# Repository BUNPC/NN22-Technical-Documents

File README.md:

This repository contains the technical documentation used to create all parts of the NN22 whole-head fNIRS system.

A description of the documents contained in this respository and other instructions related to the ninjaNIRS system can be found at openfnirs.org [here](https://openfnirs.org/hardware/ninjanirs2022/).

Please use the [Hardware Forum](https://openfnirs.org/community/hardware-forum/) at openfnirs.org to discuss anything about the ninjaNIRS system.

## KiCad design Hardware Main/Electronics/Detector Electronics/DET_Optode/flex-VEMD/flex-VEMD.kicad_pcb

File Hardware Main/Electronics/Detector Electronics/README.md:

# Detector Electronics
## Updated 5 August, 2024

All detector related files are located within this folder.

Two versions of the backplane are available, the 6 layer and single layer. The 6 layer folder contains the files for the full height backplane to allow for up to 6 detector interface cards to be connected and the single layer folder contains the files for the system configuration with only one interface card per backboard slot.

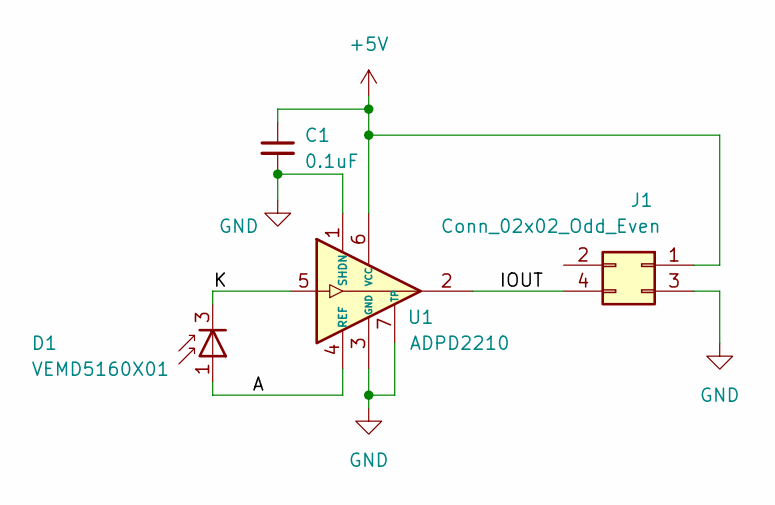
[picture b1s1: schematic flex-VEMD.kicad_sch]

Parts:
C1: 0.1uF; C_0402_1005Metric
D1: VEMD5160X01; VEMD-4-4.1x5.2mm
J1: Conn_02x02_Odd_Even; PinHeader_2x02_P1.27mm_compact
U1: ADPD2210; LFCSP-6-2x2mm

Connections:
+5V: C1.1, J1.1, U1.6 (VCC)
/A: D1.1 (A), U1.4 (REF)
/IOUT: J1.4, U1.2
/K: D1.3 (K), D1.4 (K), U1.5
GND: C1.2, J1.3, U1.1 (SHDN), U1.3 (GND), U1.7 (TP)

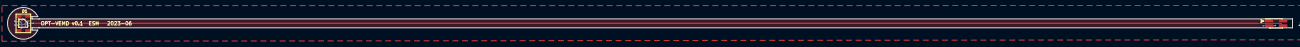
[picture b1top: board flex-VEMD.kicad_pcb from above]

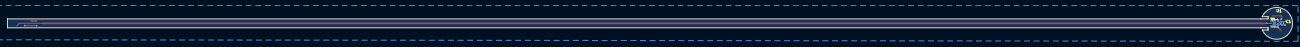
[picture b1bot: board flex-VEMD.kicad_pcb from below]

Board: 2 copper layers, 360.0 x 8.9 mm, 4 parts (2 on the bottom side), 5 nets.

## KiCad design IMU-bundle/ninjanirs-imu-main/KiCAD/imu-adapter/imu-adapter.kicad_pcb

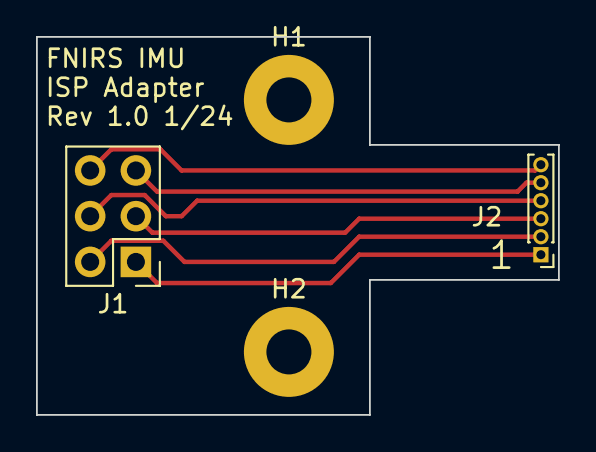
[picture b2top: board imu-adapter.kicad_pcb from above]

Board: 2 copper layers, 29.0 x 21.0 mm, 4 parts (0 on the bottom side), 6 nets.

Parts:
H1, H2: MountingHole; MountingHole_2.5mm_Pad
J1: 2x3_0.1in; PinHeader_2x03_P2.54mm_Vertical
J2: 1mm_SIP; PinHeader_1x06_P1.00mm_Vertical

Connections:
unnamed: J1.6 (GND), J2.6 (GND)
unnamed: J1.1 (MISO), J2.1 (MISO)
unnamed: J1.4 (MOSI), J2.4 (MOSI)
unnamed: J1.3 (SCK), J2.3 (SCK)
unnamed: J1.2 (VCC), J2.2 (VCC)
unnamed: J1.5 (~RST), J2.5 (~RST)

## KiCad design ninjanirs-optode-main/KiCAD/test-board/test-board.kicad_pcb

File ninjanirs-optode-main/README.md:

# ninjaNIRS optode study

  - [Flex board with Vishay photodiode](#flex-board-with-vishay-photodiode)
  - [Flex board with IQ80x photosensor](#flex-board-with-iq80x-photosensor)
  - [Readout box](#readout-box)
    - [Other devices considered](#other-devices-considered)

This repo contains work towards an implementation of an "optode" sensor unit
using off-the-shelf components.

The first design is essentially a mechanical test of the use of inexpensive
flex circuits to implement a complete optode, including connector pigtail.

## Flex board with Vishay photodiode

See `KiCAD/flex-VEMD`.

This board has a VEMD5160X01 photodiode and Analog devices ADPD2210 current amplifier.
Tests showed excessive sensitivity to 60Hz pickup, even with the flexi shielded
with copper tape.  This design has been abandoned for now (late 2023).

JLC double-layer flex has a 25um polyimide dielectric with 0.5oz copper on both sides.
There is 25um adhesive and 25um polyimide cover on each side.  Trace width is 0.5mm
with adjacent GND separated by 0.15mm.  Length 340mm.

PI dielectric constant is 3-4.

```
Parallel plate C = E(A/d) = (k * E0 * A) / d

  k = relative permittivity of dielectric (say, 3.5 for polyimide)
  E0 = permittivity of space = 8.854e-12 F/m
  A = area
  d = spacing
```

## Flex board with IQ80x photosensor

See `KiCAD/flex-IQ80xL`

This is a flexi designed for the Roithner LaserTechnik IQ80xL family of photodiodes
with integrated transimpedance amplifier.

Prototypes of two types fabricated in late 2023 with two different length flexis.
Unfortunately the pinout doesn't match the TIGRIS breakout box.  The pin numbering on the
schematics is identical (1-V-, 2-OUT, 3-V+, 4-GND) but there is an odd/even swap.

Bernhard Z has done some preliminary tests, which look promising (Dec 2023)

## Readout box

See `KiCAD/readout-box`

This is a readout box with 8 channels of TIA and LDO, to read the flex-VEMD
or other sensors with current amplifier.  Prototype built in 2023 and tested
with flex-VEMD.  Too much 60Hz pickup to pursue in this setup.
Used RT9058 LDOs and ADA4001-2 dual op-amps.

This board deliberately designed with hand-solderable parts:  SOT-23,
SO-8, 0603 passives.

### Other devices considered

This info left for reference

* THS4631 - single supply (up to +/-15V)
* LHM6611 - single supply 345MHz rail-to-rail amp (SOT-23-5)
* OPA842/3/6/7 and OPA656/7

Berhard suggests some quad options

* OPA4141 - Quad - 10MHz GBW - 36V supply - TSSOP, SOIC
* OPA2156 - Dual - 25MHz GBW - 36V supply - TSSOP, SOIC
* ADA4001-2 - Dual - 17MHz GBW - 36V supply - SOIC

Some others from a quick search:

| P/N           | GBW    | Supply | Noise                  | I(Bias) | Packages           | Notes |
|---------------|--------|--------|------------------------|---------|--------------------|-------|
| AD8672/4      | 10MHz  | 30V    | 2.8nV/Hz, 77nV p/p LF  | 12nA    | SOIC, MSOP         |       |
| ADA4004-2, -4 | 12MHz  | 30V    | 1.8nV/Hz  100nV p/p LF | 90nA    | SOIC, MSOP, LFCSP  |       |
| TLV2172/4172  | 10MHz  | 36V    | 9nV/Hz                 | 10pA    | SOIC, VSSOP, TSSOP |       |
| OPA2172       | 10MHz  | 36V    | 7nV/Hz                 | 8pA     | VSSOP, TSSOP       |       |
| OPA42140/4140 | 11MHz  | 36V    | 5.1nV/Hz  250nV p/p LF | 20pA    | TSSOP, VSSOP       |       |
| THS4032       | 100MHz | 30V    | 1.6nV/Hz               | 3uA (!) |                    |       |
| BA4560        | 10MHz  | 36V    | 8nV/Hz                 | 500nA   | TSSOP, MSOP        |       |
| BA4580        | 10MHz  | 32V    | 5nV/Hz                 | 500nA   | MSOP, SSOP         |       |
| MC33272       | 24MHz  | 36V    | 18nV/Hz                | 300nA   | TSSOP              |       |
|               |        |        |                        |         |                    |       |

Some references:

* https://www.ti.com/lit/pdf/sboa268
* https://www.electronicdesign.com/technologies/analog/article/21801223/whats-all-this-transimpedance-amplifier-stuff-anyhow-part-1

## Readout splitter

This is a new (Dec 2023) splitter box to provide the same function as the TIGRIS
box but with LDOs instead of the capacitance multipler circuits.

See [README](KiCAD/readout-box/README.md) for some more details.

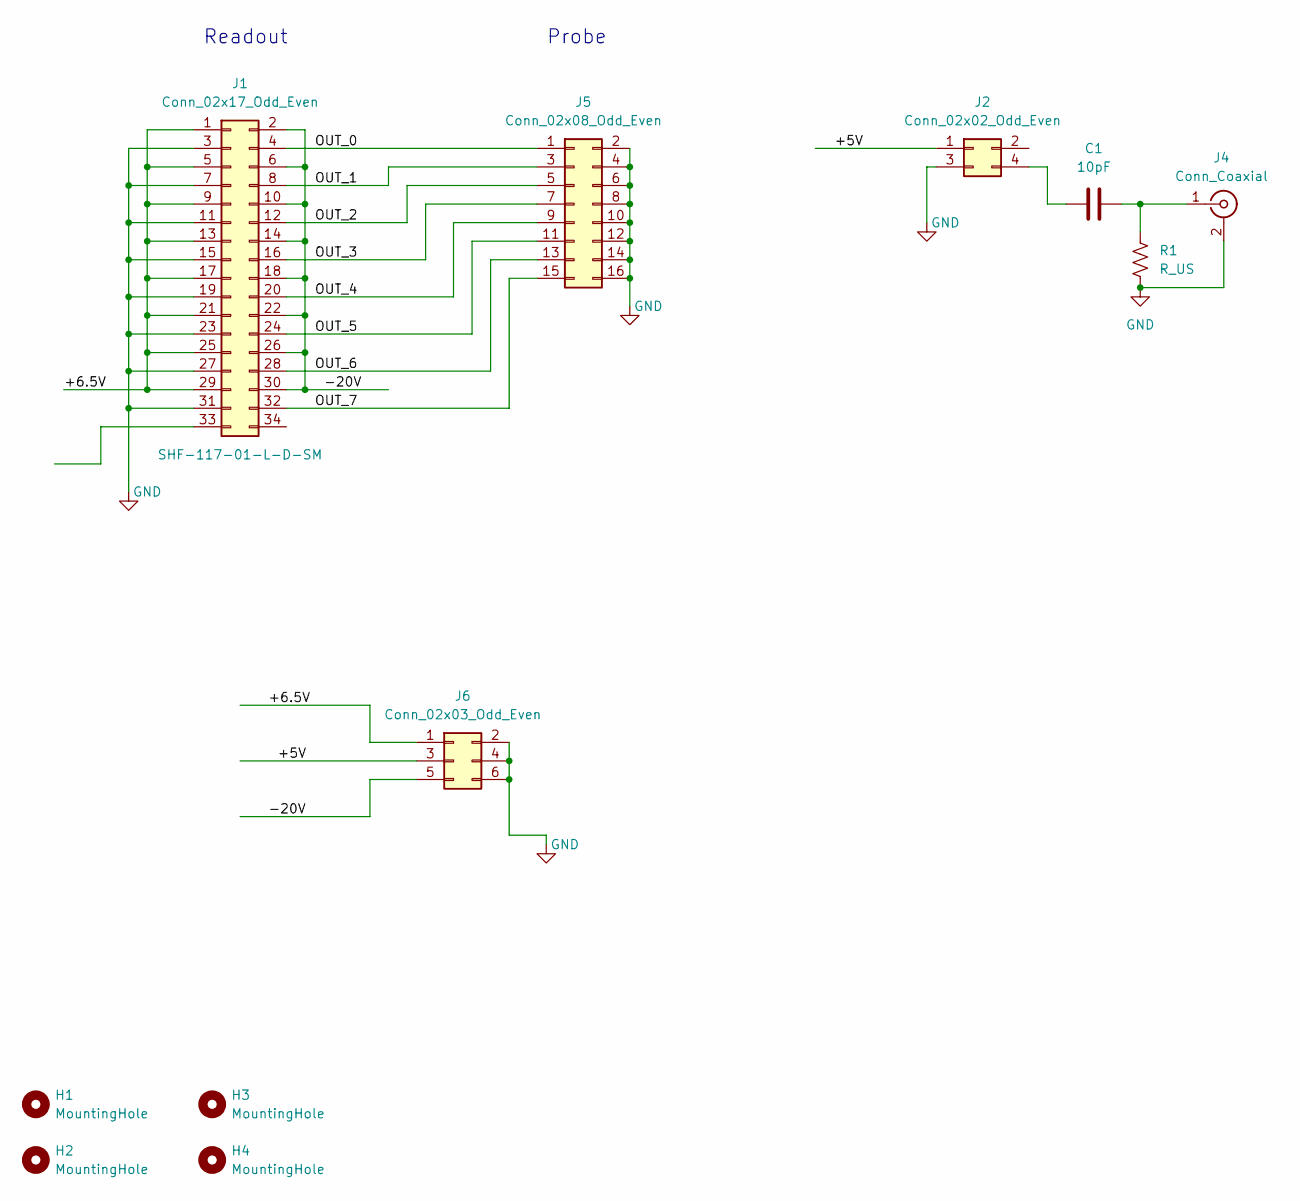
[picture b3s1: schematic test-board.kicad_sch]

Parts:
C1: 10pF; C_0603_1608Metric_Pad1.08x0.95mm_HandSolder
H1, H2, H3, H4: MountingHole; MountingHole_2.7mm_M2.5_DIN965_Pad
J1: Conn_02x17_Odd_Even; SHF-117-01-X-D-SM
J2: Conn_02x02_Odd_Even; PinHeader_2x02_P1.27mm_Vertical_SMD
J4: Conn_Coaxial; BNC_Amphenol_B6252HB-NPP3G-50_Horizontal; Manufacturers P/N RF1-01K-D-00-50-BK-HDW
J5: Conn_02x08_Odd_Even; PinHeader_2x08_P2.54mm_Vertical
J6: Conn_02x03_Odd_Even; PinHeader_2x03_P2.54mm_Vertical
R1: R_US; R_0603_1608Metric_Pad0.98x0.95mm_HandSolder

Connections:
/+5V: J2.1, J6.3
/+6.5V: J1.1, J1.5, J1.9, J1.13, J1.17, J1.21, J1.25, J1.29, J6.1
/-20V: J1.2, J1.6, J1.10, J1.14, J1.18, J1.22, J1.26, J1.30, J6.5
/OUT_0: J1.4, J5.1
/OUT_1: J1.8, J5.3
/OUT_2: J1.12, J5.5
/OUT_3: J1.16, J5.7
/OUT_4: J1.20, J5.9
/OUT_5: J1.24, J5.11
/OUT_6: J1.28, J5.13
/OUT_7: J1.32, J5.15
GND: J1.3, J1.7, J1.11, J1.15, J1.19, J1.23, J1.27, J1.31, J2.3, J4.2 (Ext), J5.2, J5.4, J5.6, J5.8, J5.10, J5.12, J5.14, J5.16, J6.2, J6.4, J6.6, R1.2
unnamed: C1.1, J2.4
unnamed: C1.2, J4.1 (In), R1.1

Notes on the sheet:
Probe
Readout

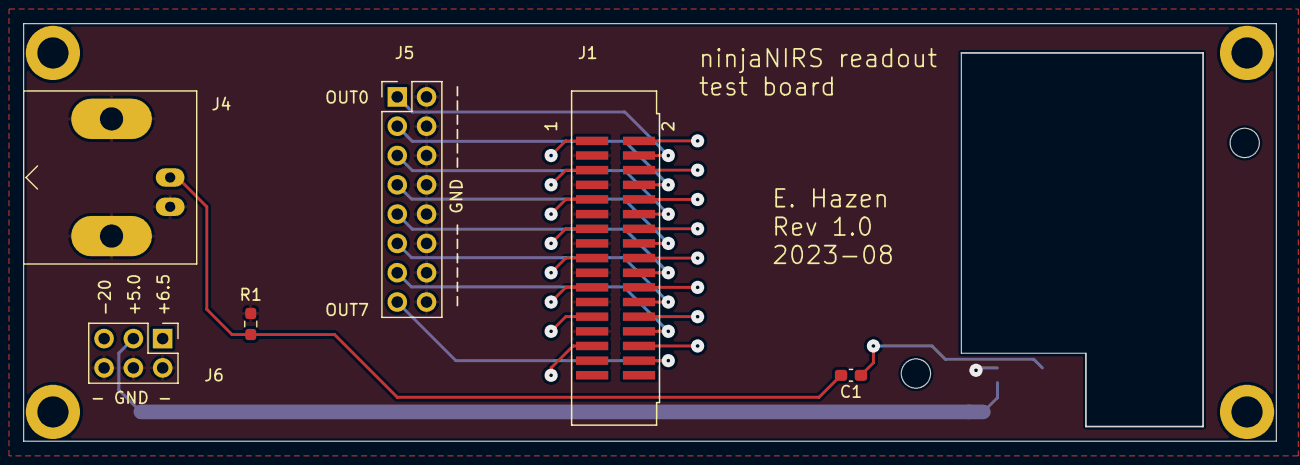
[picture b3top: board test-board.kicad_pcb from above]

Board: 4 copper layers, 108.6 x 36.2 mm, 11 parts (1 on the bottom side), 14 nets.

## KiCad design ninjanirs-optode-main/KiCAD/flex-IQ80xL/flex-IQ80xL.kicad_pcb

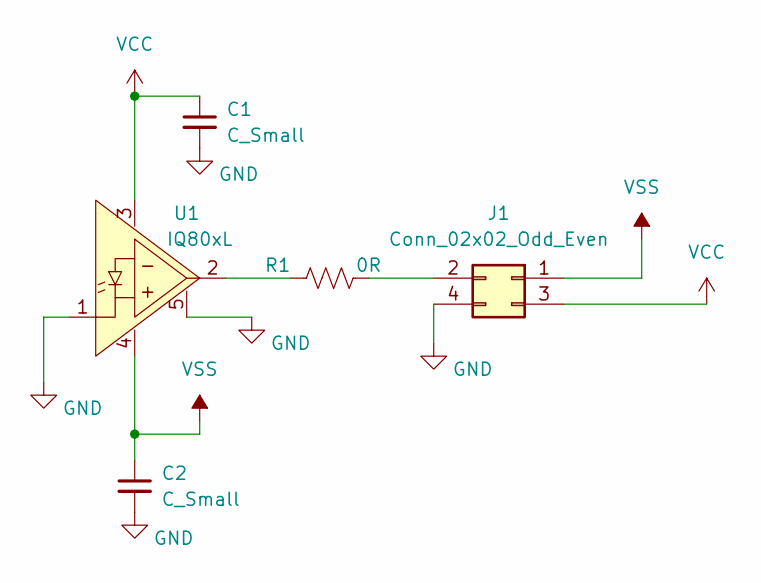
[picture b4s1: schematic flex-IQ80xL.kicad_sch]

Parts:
C1, C2: C_Small; C_0603_1608Metric
J1: Conn_02x02_Odd_Even; PinHeader_2x02_P1.27mm_compact
R1: 0R; R_0603_1608Metric
U1: IQ80xL

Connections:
GND: C1.2, C2.2, J1.4, U1.1 (GND), U1.5 (CASE)
unnamed: J1.2, R1.2
unnamed: R1.1, U1.2 (OUT)
VCC: C1.1, J1.3, U1.3 (V+)
VSS: C2.1, J1.1, U1.4 (V-)

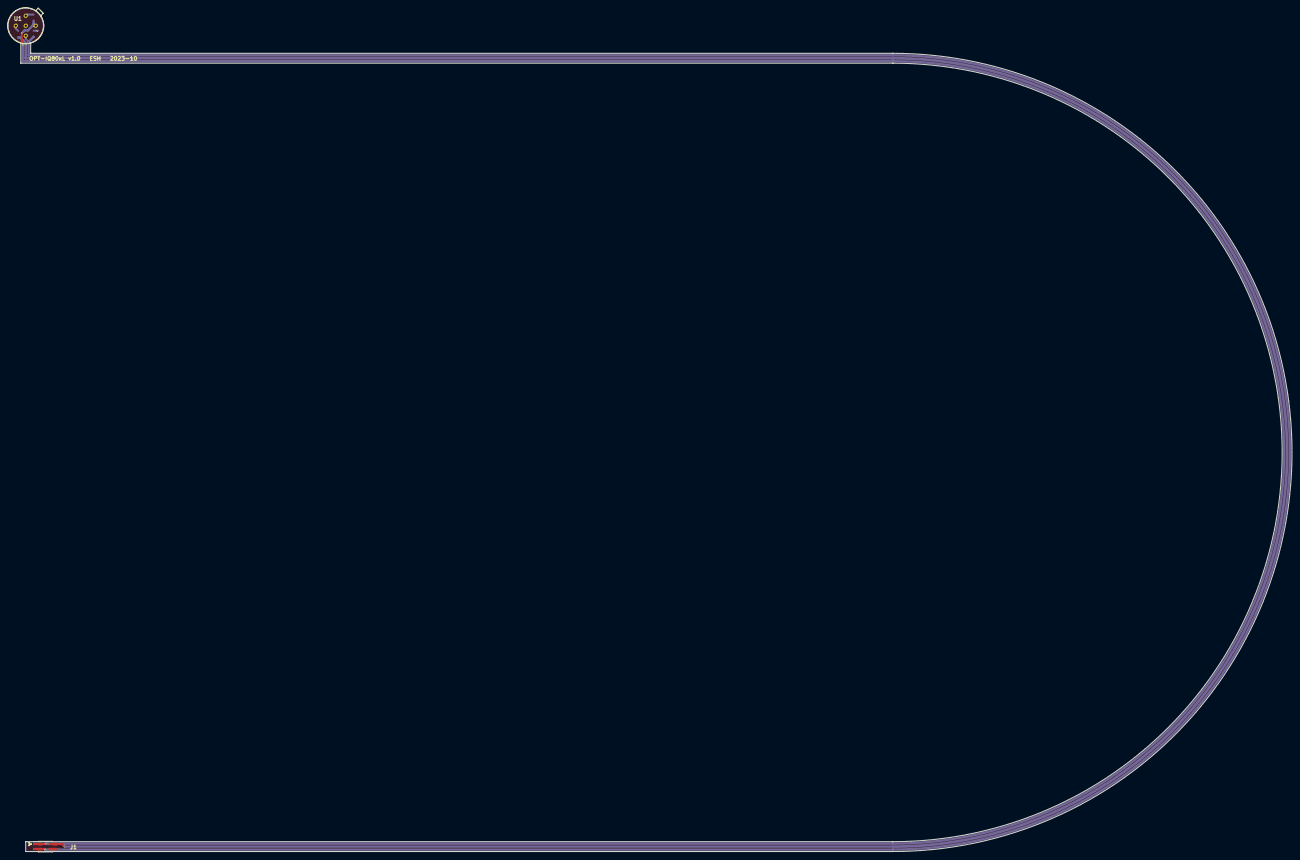
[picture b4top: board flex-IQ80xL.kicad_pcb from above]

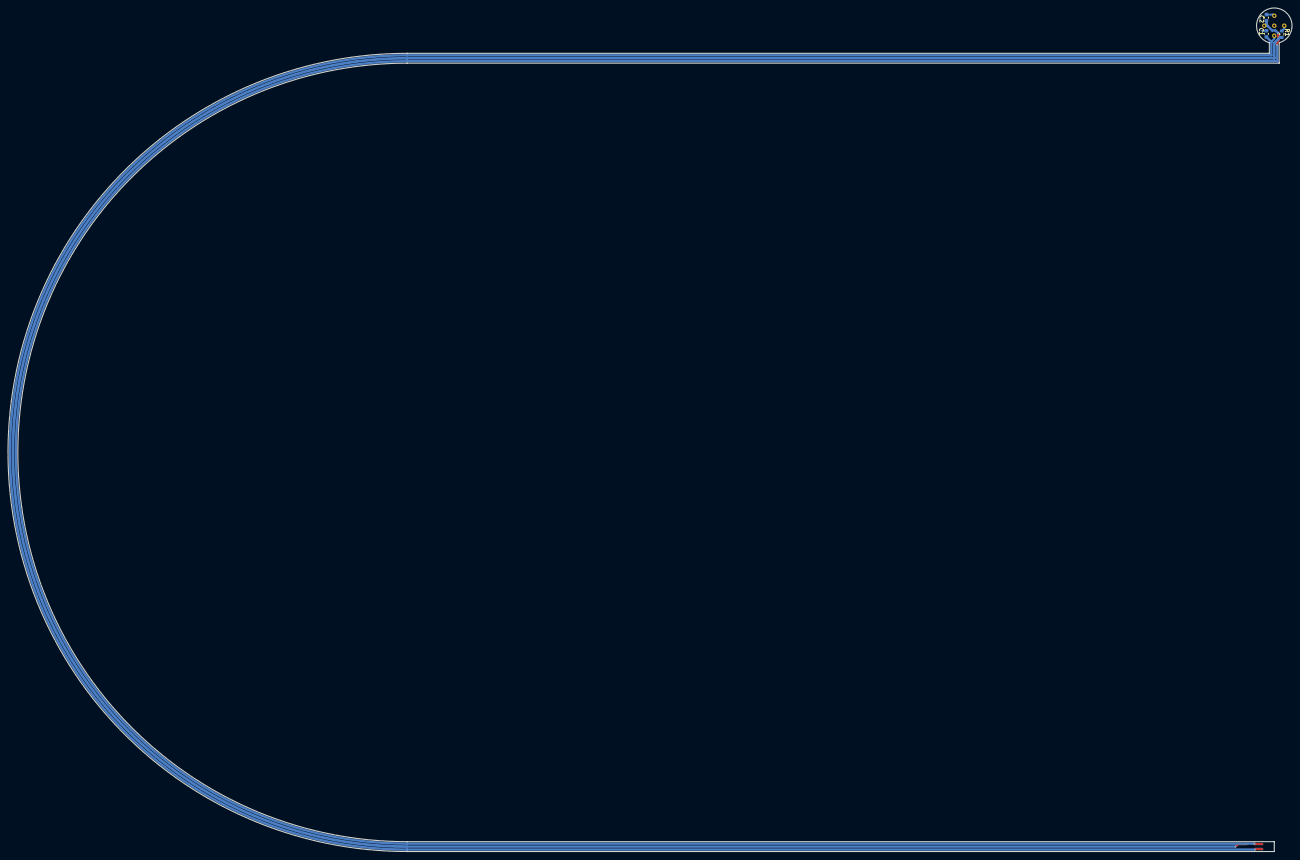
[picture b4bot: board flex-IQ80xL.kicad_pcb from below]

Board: 2 copper layers, 325.7 x 214.0 mm, 5 parts (3 on the bottom side), 5 nets.

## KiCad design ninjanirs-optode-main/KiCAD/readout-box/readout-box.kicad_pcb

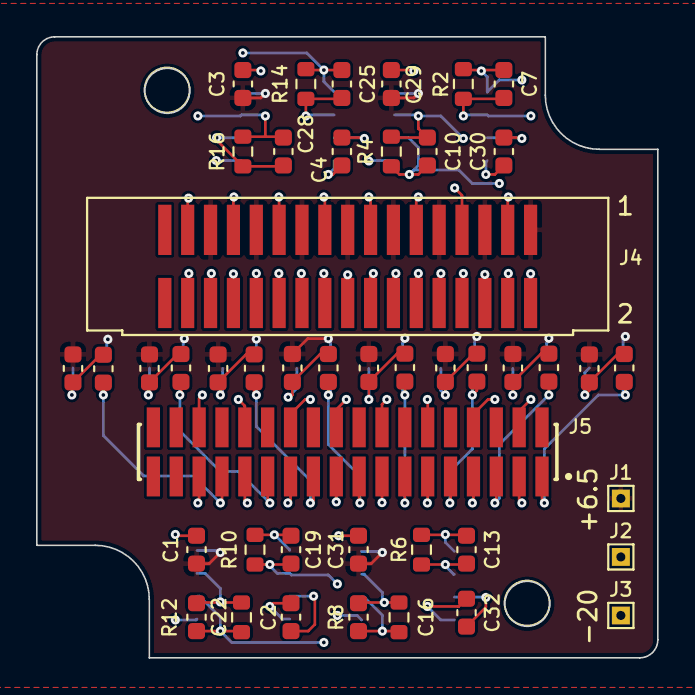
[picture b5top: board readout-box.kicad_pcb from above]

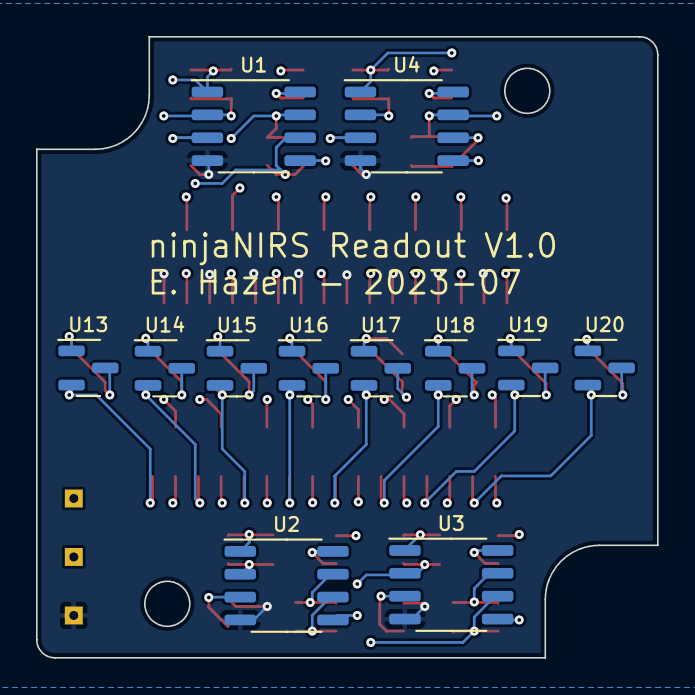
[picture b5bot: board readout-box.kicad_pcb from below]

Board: 4 copper layers, 34.5 x 34.5 mm, 58 parts (12 on the bottom side), 27 nets.

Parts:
C1, C2, C3, C4, C29, C30, C31, C32: C; C_0603_1608Metric
C5, C6, C8, C9, C11, C12, C14, C15, C17, C18, C20, C21, C23, C24, C26, C27: 1uF; C_0603_1608Metric
C7, C10, C13, C16, C19, C22, C25, C28: 1.6pF; C_0603_1608Metric
J1, J2, J3: Conn_01x01_Pin; TestPoint_THTPad_1.0x1.0mm_Drill0.5mm
J4: Conn_02x17_Odd_Even; SHF-117-01-X-D-SM
J5: Conn_02x18_Odd_Even; SAMTEC_SFMC-118-02-L-D
N1: Housing; 1551QGY
R2, R4, R6, R8, R10, R12, R14, R16: 1.0MEG; R_0603_1608Metric
U1, U2, U3, U4: ADA4001-2; SO-8_3.9x4.9mm_P1.27mm
U13, U14, U15, U16, U17, U18, U19, U20: RT9058; SOT-23

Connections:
/5V_0: C6.1, J5.1, U13.2 (VO)
/5V_1: C9.1, J5.5, U14.2 (VO)
/5V_2: C12.1, J5.9, U15.2 (VO)
/5V_3: C15.1, J5.13, U16.2 (VO)
/5V_4: C18.1, J5.17, U17.2 (VO)
/5V_5: C21.1, J5.21, U18.2 (VO)
/5V_6: C24.1, J5.25, U19.2 (VO)
/5V_7: C27.1, J5.29, U20.2 (VO)
/+6.5V: C1.1, C3.1, C5.1, C8.1, C11.1, C14.1, C17.1, C20.1, C23.1, C26.1, C29.1, C31.1, J1.1, J4.1, J4.5, J4.9, J4.13, J4.17, J4.21, J4.25, J4.29, U1.8 (V+), U2.8 (V+), U3.8 (V+), U4.8 (V+), U13.1 (VI), U14.1 (VI), U15.1 (VI), U16.1 (VI), U17.1 (VI), U18.1 (VI), U19.1 (VI), U20.1 (VI)
/-20V: C2.1, C4.1, C30.1, C32.1, J3.1, J4.2, J4.6, J4.10, J4.14, J4.18, J4.22, J4.26, J4.30, U1.4 (V-), U2.4 (V-), U3.4 (V-), U4.4 (V-)
/DET_0: C7.2, J5.4, R2.1, U1.2 (-)
/DET_1: C10.2, J5.8, R4.1, U1.6 (-)
/DET_2: C13.2, J5.12, R6.1, U2.2 (-)
/DET_3: C16.2, J5.16, R8.1, U2.6 (-)
/DET_4: C19.2, J5.20, R10.1, U3.2 (-)
/DET_5: C22.2, J5.24, R12.1, U3.6 (-)
/DET_6: C25.2, J5.28, R14.1, U4.2 (-)
/DET_7: C28.2, J5.32, R16.1, U4.6 (-)
/OUT_0: C7.1, J4.4, R2.2, U1.1
/OUT_1: C10.1, J4.8, R4.2, U1.7
/OUT_2: C13.1, J4.12, R6.2, U2.1
/OUT_3: C16.1, J4.16, R8.2, U2.7
/OUT_4: C19.1, J4.20, R10.2, U3.1
/OUT_5: C22.1, J4.24, R12.2, U3.7
/OUT_6: C25.1, J4.28, R14.2, U4.1
/OUT_7: C28.1, J4.32, R16.2, U4.7
GND: C1.2, C2.2, C3.2, C4.2, C5.2, C6.2, C8.2, C9.2, C11.2, C12.2, C14.2, C15.2, C17.2, C18.2, C20.2, C21.2, C23.2, C24.2, C26.2, C27.2, C29.2, C30.2, C31.2, C32.2, J2.1, J4.3, J4.7, J4.11, J4.15, J4.19, J4.23, J4.27, J4.31, J5.3, J5.7, J5.11, J5.15, J5.19, J5.23, J5.27, J5.31, U1.3 (+), U1.5 (+), U2.3 (+), U2.5 (+), U3.3 (+), U3.5 (+), U4.3 (+), U4.5 (+), U13.3 (GND), U14.3 (GND), U15.3 (GND), U16.3 (GND), U17.3 (GND), U18.3 (GND), U19.3 (GND), U20.3 (GND)

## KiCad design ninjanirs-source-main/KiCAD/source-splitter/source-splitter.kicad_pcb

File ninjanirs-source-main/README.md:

# ninjanirs-source

Source optode and splitter box designs

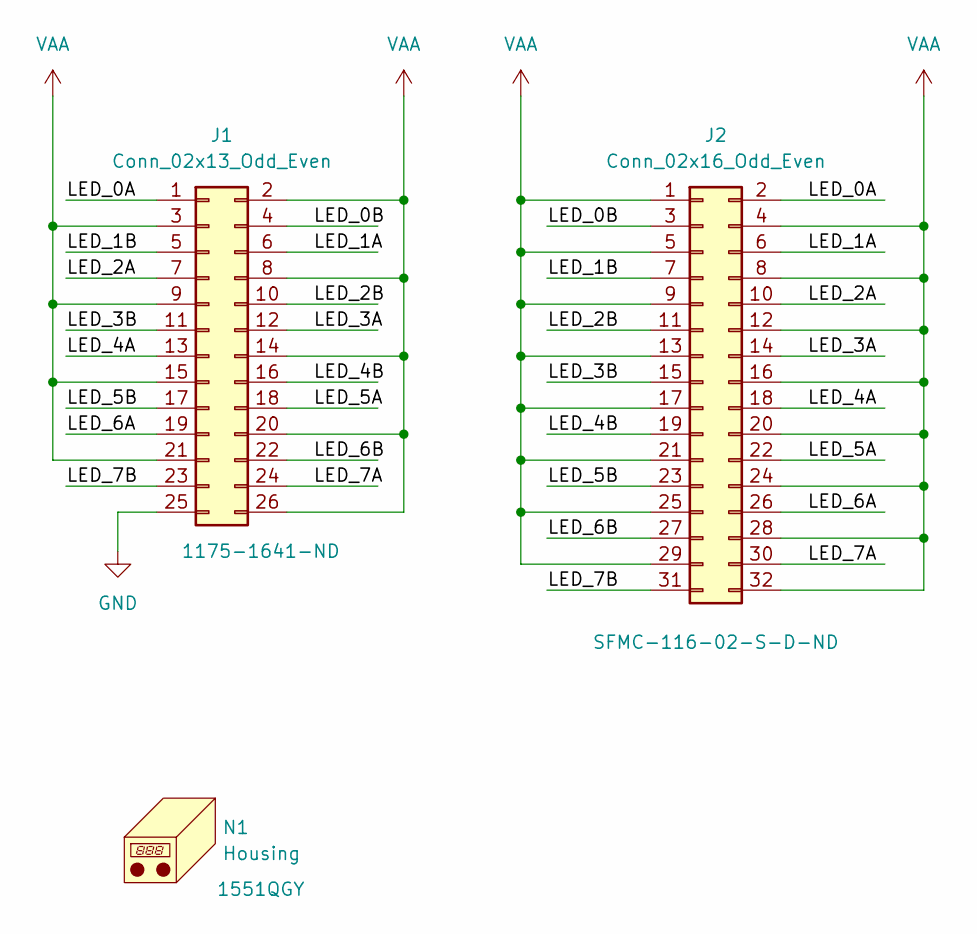
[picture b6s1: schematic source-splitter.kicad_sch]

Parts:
J1: Conn_02x13_Odd_Even; SAMTEC_SHF-113-01-L-D-SM
J2: Conn_02x16_Odd_Even; SAMTEC_SFMC-116-02-S-D_swap12
N1: Housing; 1551QGY

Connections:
/LED_0A: J1.1, J2.2
/LED_0B: J1.4, J2.3
/LED_1A: J1.6, J2.6
/LED_1B: J1.5, J2.7
/LED_2A: J1.7, J2.10
/LED_2B: J1.10, J2.11
/LED_3A: J1.12, J2.14
/LED_3B: J1.11, J2.15
/LED_4A: J1.13, J2.18
/LED_4B: J1.16, J2.19
/LED_5A: J1.18, J2.22
/LED_5B: J1.17, J2.23
/LED_6A: J1.19, J2.26
/LED_6B: J1.22, J2.27
/LED_7A: J1.24, J2.30
/LED_7B: J1.23, J2.31
GND: J1.25
VAA: J1.2, J1.3, J1.8, J1.9, J1.14, J1.15, J1.20, J1.21, J1.26, J2.1, J2.4, J2.5, J2.8, J2.9, J2.12, J2.13, J2.16, J2.17, J2.20, J2.21, J2.24, J2.25, J2.28, J2.29, J2.32

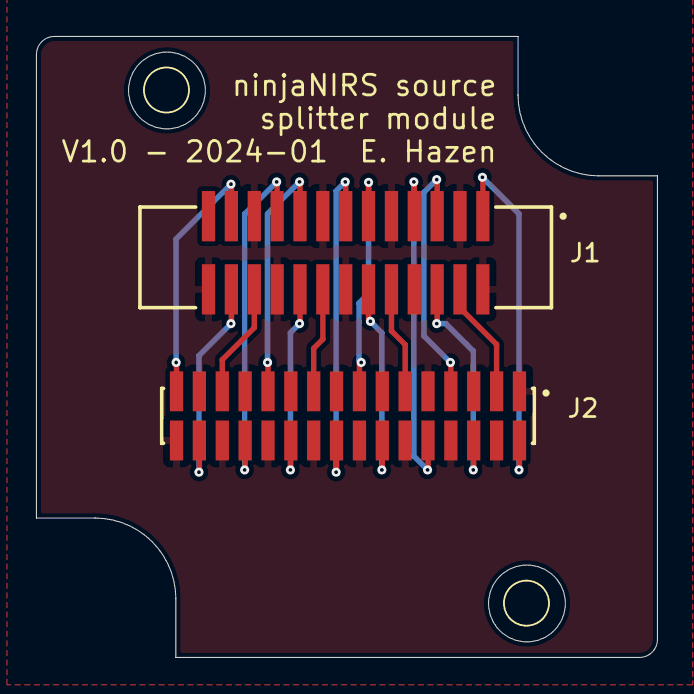
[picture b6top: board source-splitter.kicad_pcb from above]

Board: 2 copper layers, 34.5 x 34.5 mm, 3 parts (0 on the bottom side), 17 nets.

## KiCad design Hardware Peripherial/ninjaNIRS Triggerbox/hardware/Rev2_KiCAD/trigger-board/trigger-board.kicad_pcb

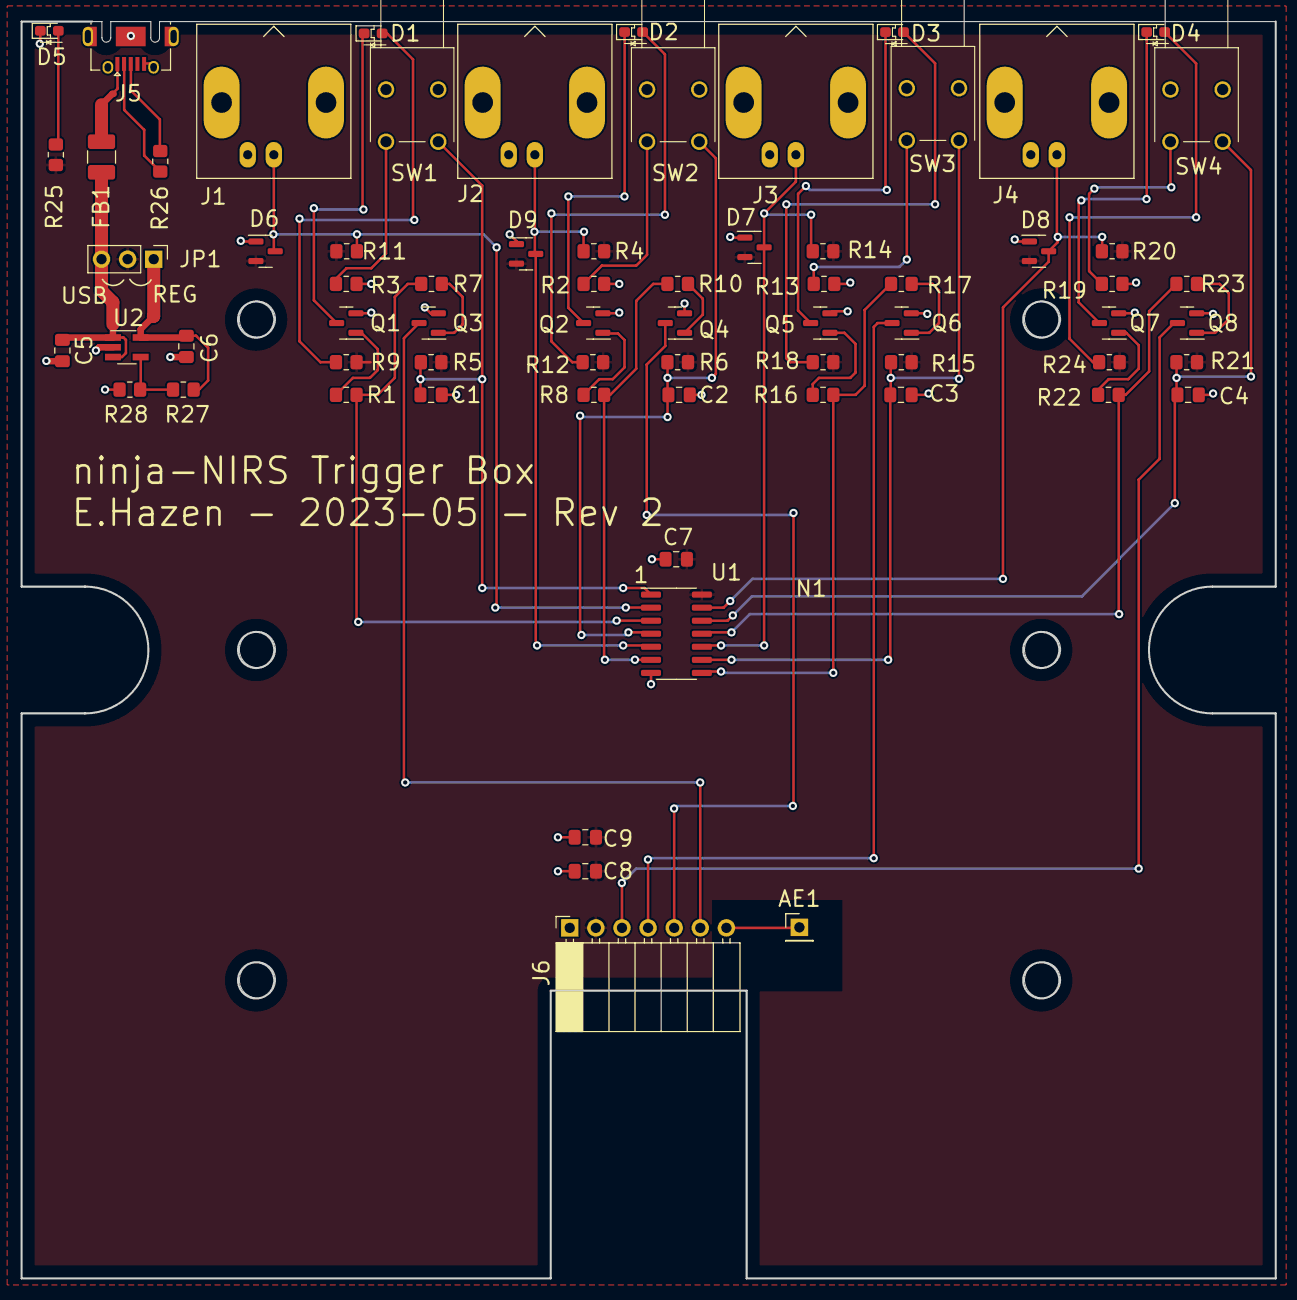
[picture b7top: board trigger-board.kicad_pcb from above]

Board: 2 copper layers, 122.0 x 122.3 mm, 70 parts (0 on the bottom side), 46 nets.

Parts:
AE1: Antenna; PinHeader_1x01_P2.54mm_Vertical
C1, C2, C3, C4: 47nF; C_0805_2012Metric_Pad1.18x1.45mm_HandSolder
C5, C6: 1uF; C_0805_2012Metric_Pad1.18x1.45mm_HandSolder
C7, C9: 0.1uF; C_0805_2012Metric_Pad1.18x1.45mm_HandSolder
C8: 10uF; C_0805_2012Metric_Pad1.18x1.45mm_HandSolder
D1, D2, D3, D4, D5: LED; LED_0603_marked
D6, D7, D8, D9: BAV99; SOT-23
FB1: FerriteBead_Small; L_1210_3225Metric_Pad1.42x2.65mm_HandSolder
J1, J2, J3, J4: Conn_Coaxial; BNC_Amphenol_B6252HB-NPP3G-50_Horizontal
J5: USB_B_Micro; USB_Micro-AB_Molex_47590-0001
J6: Conn_01x07; PinSocket_1x07_P2.54mm_Horizontal
JP1: Jumper_3_Open; PinHeader_1x03_P2.54mm_Vertical
N1: Hammond 1598BBK; Hammond_1598B
Q1, Q2, Q3, Q4, Q5, Q6, Q7, Q8: MMBT3904; SOT-23
R1, R7, R8, R10, R16, R17, R22, R23, R28: 10.0k 1%; R_0805_2012Metric_Pad1.20x1.40mm_HandSolder
R2, R3, R13, R19, R26: 100; R_0805_2012Metric_Pad1.20x1.40mm_HandSolder
R4, R5, R6, R11, R14, R15, R20, R21: 10k; R_0805_2012Metric_Pad1.20x1.40mm_HandSolder
R9, R12, R18, R24: 3.3k; R_0805_2012Metric_Pad1.20x1.40mm_HandSolder
R25: 1k; R_0805_2012Metric_Pad1.20x1.40mm_HandSolder
R27: 24.0k 1%; R_0805_2012Metric_Pad1.20x1.40mm_HandSolder
SW1, SW2, SW3, SW4: SW_Push; 800SP9B6M6RE
U1: SN74HCS00; SOIC-14_3.9x8.7mm_P1.27mm
U2: MIC5318; SOT-23-5_HandSoldering

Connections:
+5V: C7.1, C8.1, C9.1, D6.2 (A), D7.2 (A), D8.2 (A), D9.2 (A), J6.2, JP1.2 (C), R4.2, R5.2, R6.2, R9.1, R11.2, R12.1, R14.2, R15.2, R18.1, R20.2, R21.2, R24.1, R25.1, U1.14 (VCC)
/TX1: J6.6, Q3.3 (C)
/TX2: J6.5, Q4.3 (C)
/TX3: J6.4, Q6.3 (C)
/TX4: J6.3, Q8.3 (C)
GND: C1.2, C2.2, C3.2, C4.2, C5.2, C6.2, C7.2, C8.2, C9.2, D5.1 (K), D6.1 (K), D7.1 (K), D8.1 (K), D9.1 (K), J1.2 (Ext), J2.2 (Ext), J3.2 (Ext), J4.2 (Ext), J5.5 (GND), J5.6 (Shield), J6.1, Q1.2 (E), Q2.2 (E), Q3.2 (E), Q4.2 (E), Q5.2 (E), Q6.2 (E), Q7.2 (E), Q8.2 (E), R2.2, R3.2, R13.2, R19.2, R28.1, U1.7 (GND), U2.2 (GND)
unnamed: AE1.1 (A), J6.7
unnamed: C1.1, R5.1, SW1.2, U1.1
unnamed: C2.1, R6.1, SW2.2, U1.4
unnamed: C3.1, R15.1, SW3.2, U1.9
unnamed: C4.1, R21.1, SW4.2, U1.12
unnamed: D1.2 (A), R9.2
unnamed: D1.1 (K), Q1.3 (C)
unnamed: D2.2 (A), R12.2
unnamed: D2.1 (K), Q2.3 (C)
unnamed: D3.2 (A), R18.2
unnamed: D3.1 (K), Q5.3 (C)
unnamed: D4.2 (A), R24.2
unnamed: D4.1 (K), Q7.3 (C)
unnamed: D5.2 (A), R25.2
unnamed: D6.3 (K), J1.1 (In), R11.1, U1.2
unnamed: D9.3 (K), J2.1 (In), R4.1, U1.5
unnamed: D7.3 (K), J3.1 (In), R14.1, U1.10
unnamed: D8.3 (K), J4.1 (In), R20.1, U1.13
unnamed: J5.3 (D+), R26.2
unnamed: J5.2 (D-), R26.1
unnamed: FB1.1, J5.1 (VBUS)
unnamed: C6.1, JP1.1 (A), R27.2, U2.5 (VOUT)
unnamed: C5.1, FB1.2, JP1.3 (B), U2.1 (VIN), U2.3 (EN)
unnamed: Q1.1 (B), R1.2
unnamed: Q2.1 (B), R8.2
unnamed: Q3.1 (B), R7.2
unnamed: Q4.1 (B), R10.2
unnamed: Q5.1 (B), R16.2
unnamed: Q6.1 (B), R17.2
unnamed: Q7.1 (B), R22.2
unnamed: Q8.1 (B), R23.2
unnamed: R1.1, R7.1, U1.3
unnamed: R2.1, SW2.1
unnamed: R3.1, SW1.1
unnamed: R8.1, R10.1, U1.6
unnamed: R13.1, SW3.1
unnamed: R16.1, R17.1, U1.8
unnamed: R19.1, SW4.1
unnamed: R22.1, R23.1, U1.11
unnamed: R27.1, R28.2, U2.4 (ADJ)

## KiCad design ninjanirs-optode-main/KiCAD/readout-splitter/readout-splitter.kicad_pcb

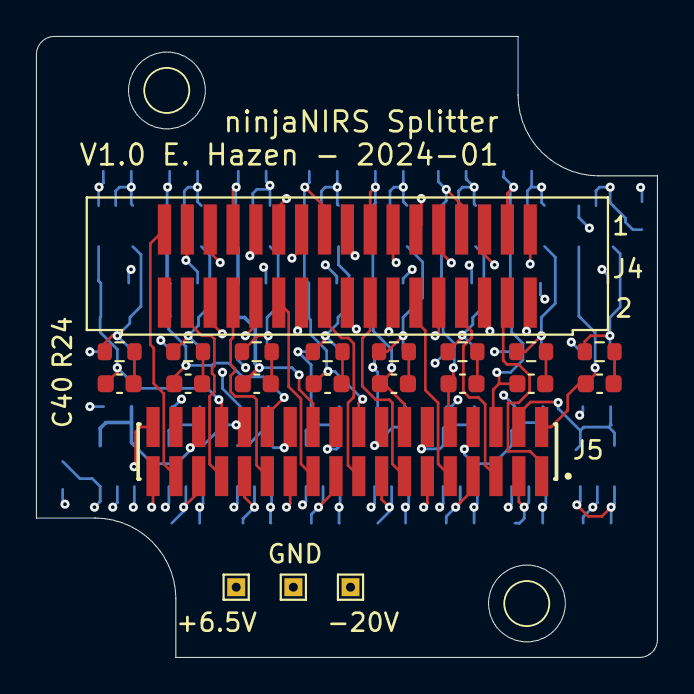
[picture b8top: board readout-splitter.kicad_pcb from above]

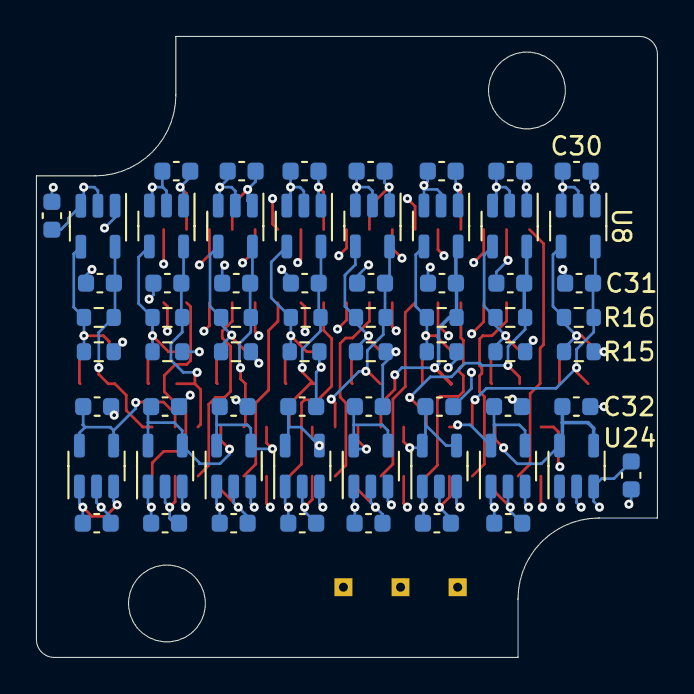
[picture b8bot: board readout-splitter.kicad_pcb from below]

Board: 4 copper layers, 34.5 x 34.5 mm, 86 parts (64 on the bottom side), 44 nets.

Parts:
C1, C2, C3, C4, C5, C6, C7, C8, C9, C10, C11, C12, C13, C14, C15, C16, C17, C18, C19, C20, C21, C22, C23, C24, C25, C26, C27, C28, C29, C30, C31, C32: 4.7uF 25V; C_0603_1608Metric
C33, C34, C35, C36, C37, C38, C39, C40: DNP; C_0603_1608Metric
J1, J2, J3: Conn_01x01_Pin; TestPoint_THTPad_1.0x1.0mm_Drill0.5mm
J4: Conn_02x17_Odd_Even; SHF-117-01-X-D-SM
J5: Conn_02x18_Odd_Even; SAMTEC_SFMC-118-02-L-D
N1: Housing; 1551QGY
R1, R3, R5, R7, R9, R11, R13, R15: 11k; R_0603_1608Metric
R2, R4, R6, R8, R10, R12, R14, R16: 150k; R_0603_1608Metric
R17, R18, R19, R20, R21, R22, R23, R24: DNP; R_0603_1608Metric
U1, U2, U3, U4, U5, U6, U7, U8: ADP7182AUJZ; TSOT-23-5
U17, U18, U19, U20, U21, U22, U23, U24: ADP7142WAUJZ-5.0; TSOT-23-5

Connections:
/+6.5V: C3.1, C5.1, C9.1, C13.1, C17.1, C21.1, C25.1, C29.1, J1.1, J4.1, J4.5, J4.9, J4.13, J4.17, J4.21, J4.25, J4.29, J5.36, U17.1 (VIN), U17.3 (EN), U18.1 (VIN), U18.3 (EN), U19.1 (VIN), U19.3 (EN), U20.1 (VIN), U20.3 (EN), U21.1 (VIN), U21.3 (EN), U22.1 (VIN), U22.3 (EN), U23.1 (VIN), U23.3 (EN), U24.1 (VIN), U24.3 (EN)
/-20V: C1.2, C6.2, C10.2, C14.2, C18.2, C22.2, C26.2, C30.2, J3.1, J4.2, J4.6, J4.10, J4.14, J4.18, J4.22, J4.26, J4.30, U1.2 (VIN), U1.3 (EN), U2.2 (VIN), U2.3 (EN), U3.2 (VIN), U3.3 (EN), U4.2 (VIN), U4.3 (EN), U5.2 (VIN), U5.3 (EN), U6.2 (VIN), U6.3 (EN), U7.2 (VIN), U7.3 (EN), U8.2 (VIN), U8.3 (EN)
/A_COMM: J4.33, J5.33
/DET_0: J4.4, J5.1
/DET_1: J4.8, J5.5
/DET_2: J4.12, J5.9
/DET_3: J4.16, J5.13
/DET_4: J4.20, J5.17
/DET_5: J4.24, J5.21
/DET_6: J4.28, J5.25
/DET_7: J4.32, J5.29
/VN_0: C2.2, C33.2, J5.2, R2.2, U1.5 (VOUT)
/VN_1: C7.2, C34.2, J5.6, R4.2, U2.5 (VOUT)
/VN_2: C11.2, C35.2, J5.10, R6.2, U3.5 (VOUT)
/VN_3: C15.2, C36.2, J5.14, R8.2, U4.5 (VOUT)
/VN_4: C19.2, C37.2, J5.18, R10.2, U5.5 (VOUT)
/VN_5: C23.2, C38.2, J5.22, R12.2, U6.5 (VOUT)
/VN_6: C27.2, C39.2, J5.26, R14.2, U7.5 (VOUT)
/VN_7: C31.2, C40.2, J5.30, R16.2, U8.5 (VOUT)
/VP_0: C4.1, J5.4, U17.4 (SENSE/ADJ), U17.5 (VOUT)
/VP_1: C8.1, J5.8, U18.4 (SENSE/ADJ), U18.5 (VOUT)
/VP_2: C12.1, J5.12, U19.4 (SENSE/ADJ), U19.5 (VOUT)
/VP_3: C16.1, J5.16, U20.4 (SENSE/ADJ), U20.5 (VOUT)
/VP_4: C20.1, J5.20, U21.4 (SENSE/ADJ), U21.5 (VOUT)
/VP_5: C24.1, J5.24, U22.4 (SENSE/ADJ), U22.5 (VOUT)
/VP_6: C28.1, J5.28, U23.4 (SENSE/ADJ), U23.5 (VOUT)
/VP_7: C32.1, J5.32, U24.4 (SENSE/ADJ), U24.5 (VOUT)
GND: C1.1, C2.1, C3.2, C4.2, C5.2, C6.1, C7.1, C8.2, C9.2, C10.1, C11.1, C12.2, C13.2, C14.1, C15.1, C16.2, C17.2, C18.1, C19.1, C20.2, C21.2, C22.1, C23.1, C24.2, C25.2, C26.1, C27.1, C28.2, C29.2, C30.1, C31.1, C32.2, J2.1, J4.3, J4.7, J4.11, J4.15, J4.19, J4.23, J4.27, J4.31, J5.3, J5.7, J5.11, J5.15, J5.19, J5.23, J5.27, J5.31, J5.35, R1.1, R3.1, R5.1, R7.1, R9.1, R11.1, R13.1, R15.1, U1.1 (GND), U2.1 (GND), U3.1 (GND), U4.1 (GND), U5.1 (GND), U6.1 (GND), U7.1 (GND), U8.1 (GND), U17.2 (GND), U18.2 (GND), U19.2 (GND), U20.2 (GND), U21.2 (GND), U22.2 (GND), U23.2 (GND), U24.2 (GND)
unnamed: C33.1, R17.2
unnamed: C34.1, R18.2
unnamed: C35.1, R19.2
unnamed: C36.1, R20.2
unnamed: C37.1, R21.2
unnamed: C38.1, R22.2
unnamed: C39.1, R23.2
unnamed: C40.1, R24.2
unnamed: R1.2, R2.1, R17.1, U1.4 (ADJ)
unnamed: R3.2, R4.1, R18.1, U2.4 (ADJ)
unnamed: R5.2, R6.1, R19.1, U3.4 (ADJ)
unnamed: R7.2, R8.1, R20.1, U4.4 (ADJ)
unnamed: R9.2, R10.1, R21.1, U5.4 (ADJ)
unnamed: R11.2, R12.1, R22.1, U6.4 (ADJ)
unnamed: R13.2, R14.1, R23.1, U7.4 (ADJ)
unnamed: R15.2, R16.1, R24.1, U8.4 (ADJ)

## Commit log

2024-02-12 Acrylic Enclosure Technical Documents
    Uploading all technical documents for the acryllic and 3D printed components in enclosure revision AB
2024-03-22 Updated Assembly Instructions 22 March 2024
2024-05-20 Add files via upload
    Adding documentation for the creation of the ninjaHarness.
2024-05-20 Add files via upload
    Updated version of Assembly Instructions with all part files and drawings 20 May, 2024.
2024-05-20 Delete Acryllic Enclosure Assembly.zip
    Removal of incorrect zip file
2024-05-22 Add Battery Box Files
    Zip files containing Solidworks 2023 parts and Eagle PCB files
2024-05-23 Add battery box BOM file
2024-05-23 Add files via upload
    Splitter box electrical circuit diagram files for sources and detectors.
2024-05-23 Add files via upload
    NN22 Control Board V4 files
2024-05-23 Add files via upload
    Detector backplane files
2024-05-23 Add files via upload
    Detector interface board files
2024-05-23 Add files via upload
    7 slot source backplane files
2024-05-23 Add files via upload
    1 slot source backplane files
2024-05-23 Add files via upload
    Source interface card files
2024-05-23 Add files via upload
    6 slot detector backplane files
2024-05-23 Organization of file system.
2024-05-24 File reorganization
2024-05-24 Source PCB File Reorganization
2024-05-28 Add files from EH.
2024-06-06 Add Firmware Folder
2024-06-09 Update README.md to link to Hardware Forum
2024-06-09 added link to nn22 page at openfnirs
2024-06-17 Add files via upload
    PDF of acrylic enclosure assembly documentation.
2024-06-17 Add Schematic PDF for battery circuit
2024-06-27 Add Detector Files
2024-06-27 Revert "Add Detector Files"
    This reverts commit e8c7ac16a3e25841cc6b62164293f4582a5eec2a.
2024-06-27 Detector File Updates
2024-07-24 Adding Control Board v2 with gerbers.
2024-07-24 Adding gerbers to backplanes.
2024-07-24 Adding gerbers to source interface card.
2024-07-24 Updating detector interface card and adding gerbers.
2024-07-25 Adding IMU interface card.
2024-07-25 ninjaPACK BOM Upload
2024-07-29 Add Colocated Source Part Files
2024-07-29 Colocation Organization
2024-07-29 Added gerbers for co-located source optode.
2024-07-29 Adder gerbers for source optode pcb.
2024-08-05 File system reorganization
2024-08-05 Fix Flex Optode Folder
2024-08-06 Add Standard Detector Files
2024-08-29 Remove Old FIles
2025-02-18 Firmware added
